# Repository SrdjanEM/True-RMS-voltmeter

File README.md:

# Voltage Measurement System with LED Display

## Overview
This project presents a comprehensive solution for measuring and displaying AC voltage levels accurately. Utilizing the ICL7107 analog-to-digital converter (ADC) with a precision of 3½ digits, the system offers high-precision voltage readings in a digital format, directly interfacing with LED displays for easy readability. Designed for minimal power consumption, it is particularly suited for battery-operated devices.

## Key Features
- **High Precision Measurement:** Leverages the ICL7107 ADC for accurate voltage reading.
- **Efficient Display:** Features four 7-segment SA08-11YWA LED displays for clear output visibility.
- **Energy Efficient:** Optimized for low power consumption, ideal for battery-operated implementations.
- **Flexible Connectivity:** Utilizes FFC (Flat Flexible Cable) connectors for seamless integration and ease of maintenance.
- **Robust PCB Design:** A dual-layer PCB design with a focus on electromagnetic stability and efficiency. Features copper pours for GND on the back layer to enhance device reliability.

## Hardware Components
- **ICL7107 ADC:** The core component for analog-to-digital conversion, offering direct connectivity to LED displays.
- **AD737:** Outputs RMS value of the measured AC voltage, interfaced with the ICL7107.
- **SA08-11YWA LED Displays:** Four 7-segment displays with common anode configuration, powered by 5V.
- **FFC Connectors:** Provides a flexible and secure connection between the LED displays and the main PCB.
- **PCB Materials:** Utilizes FR4 for the dielectric layer and ENIG (Electroless Nickel Immersion Gold) for the copper surface finish for enhanced durability and solderability.

## Full schematic 

## PCB

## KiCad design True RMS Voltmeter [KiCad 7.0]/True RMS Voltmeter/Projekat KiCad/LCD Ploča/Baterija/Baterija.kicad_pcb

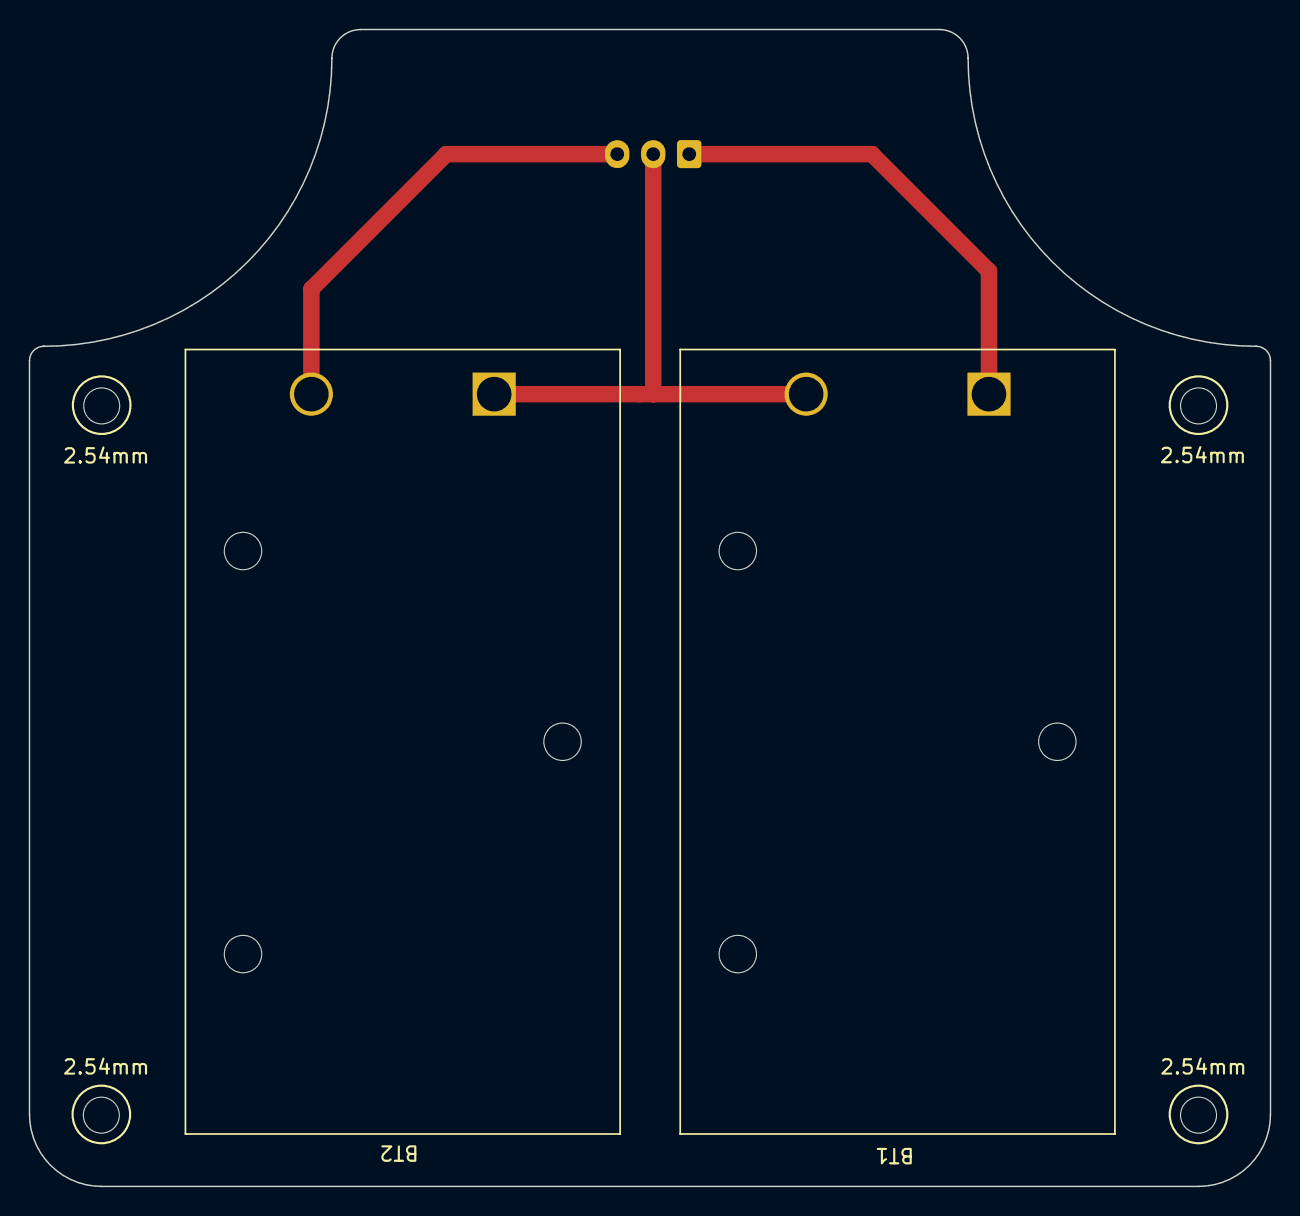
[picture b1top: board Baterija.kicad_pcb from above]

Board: 2 copper layers, 86.2 x 80.4 mm, 7 parts (1 on the bottom side), 3 nets.

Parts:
BT1, BT2: Battery; BatteryHolder_Eagle_12BH611-GR
H1, H2, H3, H4: MountingHole; MountingHole_2.5mm
J1: Battery Connector; JST_XH_B3B-XH-A_1x03_P2.50mm_Vertical

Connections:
GND: BT1.2 (-), BT2.1 (+), J1.2
unnamed: BT1.1 (+), J1.1
unnamed: BT2.2 (-), J1.3

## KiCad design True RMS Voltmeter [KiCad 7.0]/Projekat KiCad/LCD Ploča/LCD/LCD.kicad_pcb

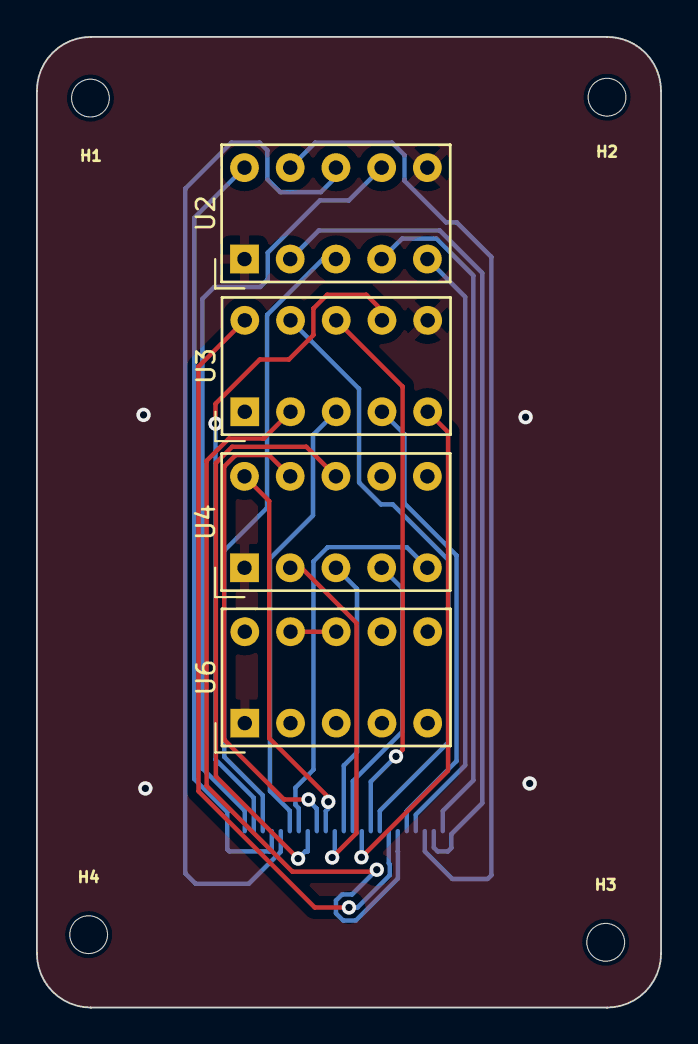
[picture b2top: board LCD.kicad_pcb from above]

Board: 2 copper layers, 34.7 x 53.9 mm, 9 parts (1 on the bottom side), 25 nets.

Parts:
H1, H2, H3, H4: MountingHole; MountingHole_2.1mm
J1: FFC Connector; FPC_24
U2, U3, U4, U6: HDSP-7401

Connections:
20V_RANGE: J1.23, U2.7 (DP)
200V_RANGE: J1.22, U3.7 (DP)
+5V: J1.24, U2.1 (CA), U2.6 (CA), U3.1 (CA), U3.6 (CA), U4.1 (CA), U4.6 (CA), U6.1 (CA), U6.6 (CA)
ICL7107_A1: J1.14, U4.10 (A)
ICL7107_A2: J1.7, U3.10 (A)
ICL7107_A3: J1.20, U2.10 (A)
ICL7107_AB4: U6.8 (C), U6.9 (B)
ICL7107_B1: J1.15, U4.9 (B)
ICL7107_B2: J1.8, U3.9 (B)
ICL7107_B3: J1.3, U2.9 (B)
ICL7107_C1: J1.16, U4.8 (C)
ICL7107_C2: J1.9, U3.8 (C)
ICL7107_C3: J1.19, U2.8 (C)
ICL7107_D1: J1.17, U4.5 (D)
ICL7107_D2: J1.10, U3.5 (D)
ICL7107_D3: J1.4, U2.5 (D)
ICL7107_E1: J1.11, U4.4 (E)
ICL7107_E2: J1.5, U3.4 (E)
ICL7107_E3: J1.1, U2.4 (E)
ICL7107_F1: J1.13, U4.2 (F)
ICL7107_F2: J1.6, U3.2 (F)
ICL7107_F3: J1.2, U2.2 (F)
ICL7107_G1: J1.12, U4.3 (G)
ICL7107_G2: J1.18, U3.3 (G)
ICL7107_G3: J1.21, U2.3 (G)

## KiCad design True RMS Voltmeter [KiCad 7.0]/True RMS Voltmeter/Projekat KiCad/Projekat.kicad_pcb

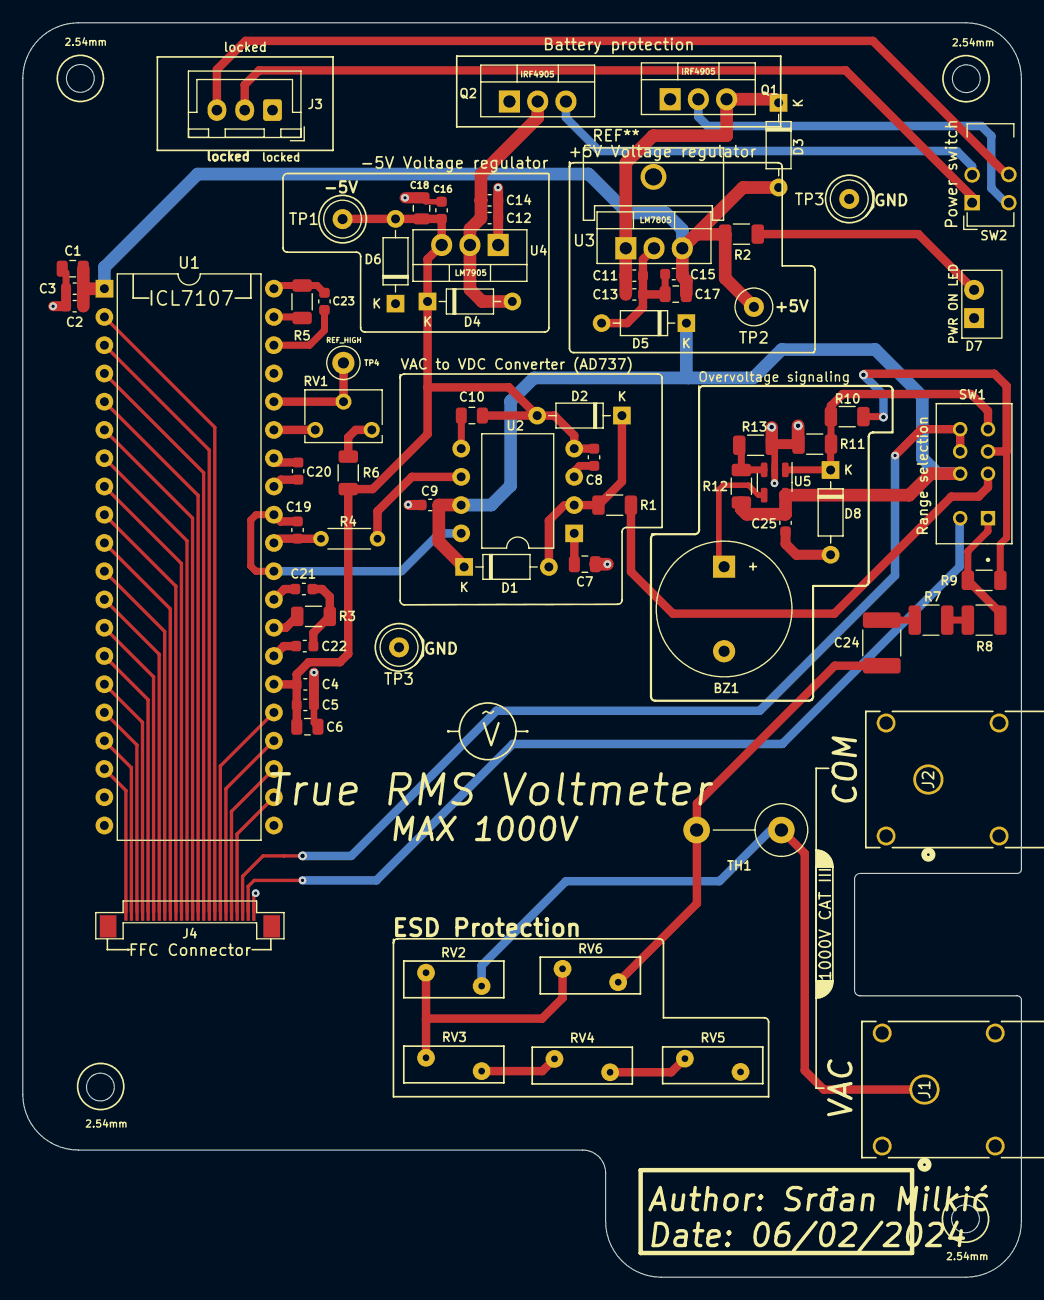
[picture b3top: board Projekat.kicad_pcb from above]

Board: 2 copper layers, 89.8 x 112.8 mm, 76 parts (0 on the bottom side), 63 nets.

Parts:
BZ1: Buzzer; Buzzer_12x9.5RM7.6
C1, C6, C7: 10u; C_0805_2012Metric
C2, C3, C4, C5, C8, C9, C13, C14, C15, C16, C20, C25: 100n; C_0603_1608Metric
C10: 3u3; C_0805_2012Metric
C11, C12: 100u; C_0603_1608Metric
C17, C18: 1u; C_0805_2012Metric
C19: 20p; C_0603_1608Metric
C21: 470n; C_0603_1608Metric
C22: 220n; C_0603_1608Metric
C23: 100p; C_0603_1608Metric
C24: 22n; C_1812_4532Metric
D1, D2: 1N4148; D_DO-35_SOD27_P7.62mm_Horizontal
D3, D4, D5, D6: 1N4448; D_DO-35_SOD27_P7.62mm_Horizontal
D7: Power ON; LED_D5.0mm_Horizontal_O6.35mm_Z15.0mm
D8: 1N5712; D_DO-35_SOD27_P7.62mm_Horizontal
H1, H2, H3, H4: MountingHole; MountingHole_2.5mm
J1: VAC; CONN1_FCR7350R_CLF
J2: COMM; CONN1_FCR7350R_CLF
J3: Battery connector; JST_XH_B3B-XH-A_1x03_P2.50mm_Vertical
J4: FPC Connector; FPC_24
Q1, Q2: IRF4905; TO-220-3_Vertical
R1, R3: 47K; R_1206_3216Metric
R2: 330; R_1206_3216Metric
R4: 1M; R_Axial_DIN0204_L3.6mm_D1.6mm_P5.08mm_Horizontal
R5: 100K; R_1206_3216Metric
R6: 24K; R_1206_3216Metric
R7: 9M; R_1210_3225Metric
R8: 900K; R_1210_3225Metric
R9: 90K; R_1206_3216Metric
R10: 9K; R_1206_3216Metric
R11: 1K; R_1206_3216Metric
R12: 11K; R_1206_3216Metric
R13: 1K5; R_1206_3216Metric
RV1: Naponska referenca (100mV); Potentiometer_Bourns_3266W_Vertical
RV2, RV3, RV4, RV5, RV6: 910V; RV_Disc_D9mm_W3.3mm_P5mm
SW1: Range selection; SW_EG2310
SW2: Power ON/OFF; SW_CuK_JS202011AQN_DPDT_Angled
TH1: PTC; R_Axial_DIN0414_L11.9mm_D4.5mm_P7.62mm_Vertical
TP1, TP2, TP3, TP3#2: TestPoint; TestPoint_Loop_D2.60mm_Drill0.9mm_Beaded
TP4: TestPoint_Loop_D2.50mm_Drill1.0mm_LowProfile
U1: ICL7107CPL; DIP-40_W15.24mm
U2: AD737; DIP-8_W10.16mm
U3: L7805; TO-220-3_Vertical
U4: L7905; TO-220-3_Vertical
U5: MAX9075; SOT-23-5

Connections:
20V_RANGE: J4.23, SW1.5
1000V_RANGE: J4.22, SW1.7, SW1.8
+5V: C1.1, C2.1, C3.1, C9.1, C15.1, C17.1, C25.1, D1.1 (K), D3.2 (A), D5.1 (K), R2.1, R12.1, SW1.6, TP2.1, U1.1 (V+), U2.7 (+Vs), U3.3 (OUT), U5.5 (V+)
+9V: C11.1, C13.1, D3.1 (K), Q1.3 (S), U3.1 (IN)
-5V: C4.2, C5.2, C6.2, C8.1, C10.2, C16.1, C18.2, D2.2 (A), D4.1 (K), D6.2 (A), R6.1, TP1.1, U1.26 (V-), U2.4 (-Vs), U4.3 (VO)
-9V: C12.2, C14.1, D4.2 (A), Q2.2 (D), U4.2 (VI)
A-Z: C21.2, U1.29 (A-Z)
AD737_COM: C19.2, RV1.1, U1.30 (IN_LO), U1.32 (COMMON), U1.35 (REF_LO), U2.8 (COM)
AD737_OUTPUT: R4.2, U2.6 (OUTPUT)
BUFF: R3.1, U1.28 (BUFF)
CREF+: C20.1, U1.34 (CREF+)
CREF-: C20.2, U1.33 (CREF-)
Cc: C7.1, U2.1 (Cc)
GND: BZ1.2 (+), C1.2, C2.2, C3.2, C4.1, C5.1, C6.1, C7.2, C8.2, C9.2, C11.2, C12.1, C13.2, C14.2, C15.2, C16.2, C17.2, C18.1, C25.2, D5.2 (A), D6.1 (K), D7.1 (K), D8.2 (A), J1.2, J1.3, J1.4, J1.5, J2.1, J2.2, J2.3, J2.4, J2.5, J3.1 (Pin_3), J4.24, Q1.1 (G), Q2.1 (G), R11.2, R13.2, RV5.2, TP3.1, TP3#2.1, U1.21 (BP/GND), U2.3 (PWR_DWN), U3.2 (GND), U4.1 (GND), U5.2 (V-)
ICL7107_A1: J4.14, U1.5 (A1)
ICL7107_A2: J4.7, U1.12 (A2)
ICL7107_A3: J4.20, U1.23 (A3)
ICL7107_B1: J4.15, U1.4 (B1)
ICL7107_B2: J4.8, U1.11 (B2)
ICL7107_B3: J4.3, U1.16 (B3)
ICL7107_C1: J4.16, U1.3 (C1)
ICL7107_C2: J4.9, U1.10 (C2)
ICL7107_C3: J4.19, U1.24 (C3)
ICL7107_D1: J4.17, U1.2 (D1)
ICL7107_D2: J4.10, U1.9 (D2)
ICL7107_D3: J4.4, U1.15 (D3)
ICL7107_E1: J4.11, U1.8 (E1)
ICL7107_E2: J4.5, U1.14 (E2)
ICL7107_E3: J4.1, U1.18 (E3)
ICL7107_F1: J4.13, U1.6 (F1)
ICL7107_F2: J4.6, U1.13 (F2)
ICL7107_F3: J4.2, U1.17 (F3)
ICL7107_G1: J4.12, U1.7 (G1)
ICL7107_G2: J4.18, U1.25 (G2)
ICL7107_G3: J4.21, U1.22 (G3)
INT: C22.1, U1.27 (INT)
IN_HI: C19.1, R4.1, U1.31 (IN_HI)
unnamed: BZ1.1 (-), U5.4
unnamed: C21.1, C22.2, R3.2
unnamed: C24.1, RV6.1, TH1.2
unnamed: C24.2, R7.1
unnamed: D1.2 (A), D2.1 (K), R1.1, U2.2 (Vin)
unnamed: D7.2 (A), R2.2
unnamed: J1.1, RV2.1, TH1.1
unnamed: J3.3 (Pin_1), SW2.3
unnamed: J3.2, SW2.1
unnamed: Q1.2 (D), SW2.4
unnamed: Q2.3 (S), SW2.2
unnamed: R6.2, RV1.3
unnamed: R7.2, R8.2
unnamed: R8.1, R9.1, SW1.1
unnamed: R9.2, R10.1, SW1.3
unnamed: RV2.2, RV3.1, RV6.2
unnamed: RV3.2, RV4.1
unnamed: RV4.2, RV5.1
unnamed: C10.1, U2.5 (Cav)
unnamed: R12.2, R13.1, U5.3 (-)
OSC1: C23.1, R5.2, U1.40 (OSC1)
OSC2: R5.1, U1.39 (OSC2)
OSC3: C23.2, U1.38 (OSC3)
REF_HI: RV1.2, TP4.1, U1.36 (REF_HI)
Threshold_voltage: D8.1 (K), R10.2, R11.1, SW1.4, U5.1 (+)
Vin: R1.2, SW1.2

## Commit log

2024-03-11 KiCad files, KiCad version 7.0
2024-03-11 Fixing double upload
2024-03-11 Images
    Images for PCB and SCH
2024-03-11 Rename Full schematic.png to FullSchematic.png
2024-03-11 Rename PCB no components.png to PCBnocomponents.png
2024-03-11 Rename PCB with components.png to PCBwithcomponents.png
2024-03-11 !Add Full schematic PDF
    For better quality
2024-05-08 Removed unused files
